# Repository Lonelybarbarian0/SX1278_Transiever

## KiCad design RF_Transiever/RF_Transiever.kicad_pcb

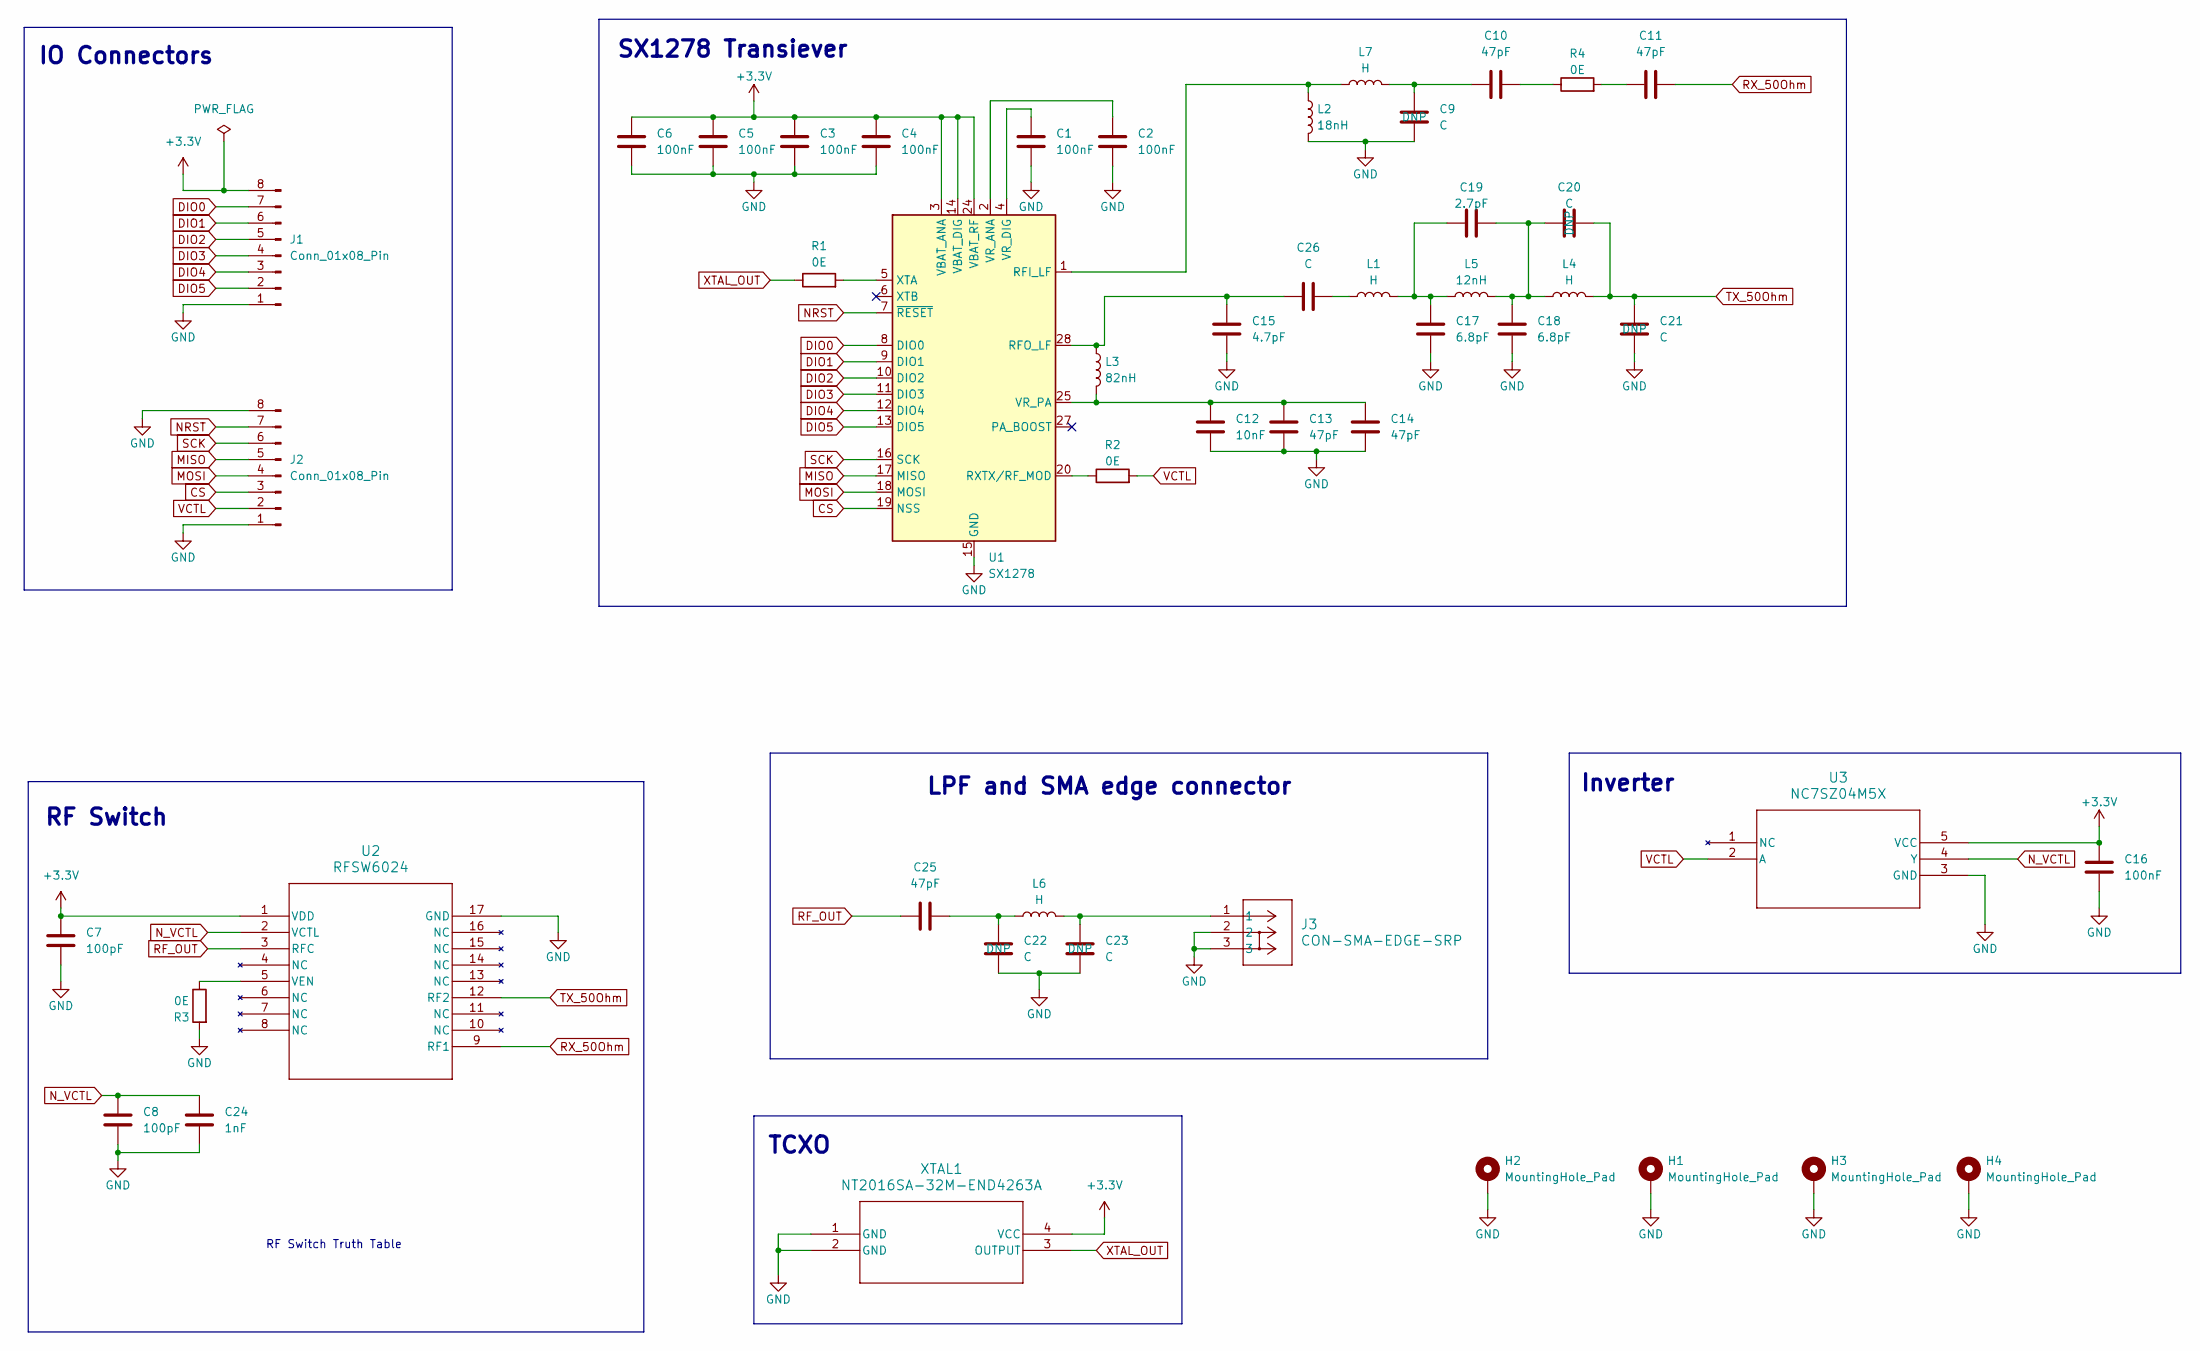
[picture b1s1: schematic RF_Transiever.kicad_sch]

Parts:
C1, C2, C3, C4, C5, C6, C16: 100nF; C_0402_1005Metric
C7, C8: 100pF; C_0402_1005Metric
C9, C20, C21, C22, C23, C26: C; C_0402_1005Metric
C10, C11, C13, C14, C25: 47pF; C_0402_1005Metric
C12: 10nF; C_0402_1005Metric
C15: 4.7pF; C_0402_1005Metric
C17, C18: 6.8pF; C_0402_1005Metric
C19: 2.7pF; C_0402_1005Metric
C24: 1nF; C_0402_1005Metric
H1, H2, H3, H4: MountingHole_Pad; MountingHole_2.2mm_M2_Pad
J1, J2: Conn_01x08_Pin; PinHeader_1x08_P2.54mm_Vertical
J3: CON-SMA-EDGE-SRP; CON-SMA-EDGE-SRP_RFS
L1, L4, L6, L7: H; L_0402_1005Metric
L2: 18nH; L_0402_1005Metric
L3: 82nH; L_0402_1005Metric
L5: 12nH; L_0402_1005Metric
R1, R2, R3: 0E; R_0603_1608Metric
R4: 0E; R_0402_1005Metric
U1: SX1278; QFN-28-1EP_6x6mm_P0.65mm_EP4.8x4.8mm
U2: RFSW6024; QFN16_4X4_QOR
U3: NC7SZ04M5X; SC-74A-5_1P65X3P15_ONS
XTAL1: NT2016SA-32M-END4263A; NT2016SA-32M-END4263A_NDK

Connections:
+3.3V: C3.1, C4.1, C5.1, C6.1, C7.1, C16.1, J1.8, U1.3 (VBAT_ANA), U1.14 (VBAT_DIG), U1.24 (VBAT_RF), U2.1 (VDD), U3.5 (VCC), XTAL1.4 (VCC)
CS: J2.3, U1.19 (NSS)
DIO0: J1.7, U1.8 (DIO0)
DIO1: J1.6, U1.9 (DIO1)
DIO2: J1.5, U1.10 (DIO2)
DIO3: J1.4, U1.11 (DIO3)
DIO4: J1.3, U1.12 (DIO4)
DIO5: J1.2, U1.13 (DIO5)
GND: C1.2, C2.2, C3.2, C4.2, C5.2, C6.2, C7.2, C8.2, C9.2, C12.2, C13.2, C14.2, C15.2, C16.2, C17.2, C18.2, C21.2, C22.2, C23.2, C24.2, H1.1, H2.1, H3.1, H4.1, J1.1, J2.1, J2.8, J3.2, J3.3, L2.2, R3.2, U1.15 (GND), U1.21 (GND), U1.22 (GND), U1.23 (GND), U1.26 (GND), U1.29 (GND), U2.17 (GND), U3.3 (GND), XTAL1.1 (GND), XTAL1.2 (GND)
MISO: J2.5, U1.17 (MISO)
MOSI: J2.4, U1.18 (MOSI)
NRST: J2.7, U1.7 (~RESET)
N_VCTL: C8.1, C24.1, U2.2 (VCTL), U3.4 (Y)
unnamed: C9.1, C10.1, L7.2
unnamed: C10.2, R4.1
unnamed: C11.1, R4.2
unnamed: C17.1, C19.1, L1.2, L5.1
unnamed: C18.1, C19.2, C20.1, L4.1, L5.2
unnamed: C22.1, C25.2, L6.1
unnamed: C23.1, J3.1, L6.2
unnamed: C26.2, L1.1
unnamed: L2.1, L7.1, U1.1 (RFI_LF)
unnamed: C15.1, C26.1, L3.1, U1.28 (RFO_LF)
unnamed: R2.1, U1.20 (RXTX/RF_MOD)
unnamed: C2.1, U1.2 (VR_ANA)
unnamed: C1.1, U1.4 (VR_DIG)
unnamed: C12.1, C13.1, C14.1, L3.2, U1.25 (VR_PA)
unnamed: R1.2, U1.5 (XTA)
unnamed: R3.1, U2.5 (VEN)
RF_OUT: C25.1, U2.3 (RFC)
RX_50Ohm: C11.2, U2.9 (RF1)
SCK: J2.6, U1.16 (SCK)
TX_50Ohm: C20.2, C21.1, L4.2, U2.12 (RF2)
VCTL: J2.2, R2.2, U3.2 (A)
XTAL_OUT: R1.1, XTAL1.3 (OUTPUT)

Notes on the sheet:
IO Connectors
Inverter
SX1278 Transiever
LPF and SMA edge connector
TCXO
RF Switch Truth Table
RF Switch

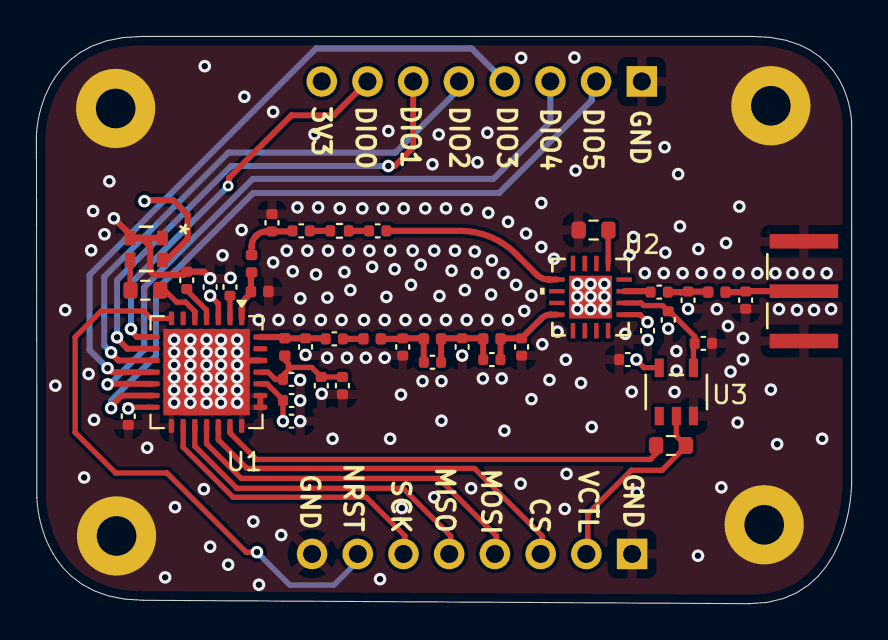
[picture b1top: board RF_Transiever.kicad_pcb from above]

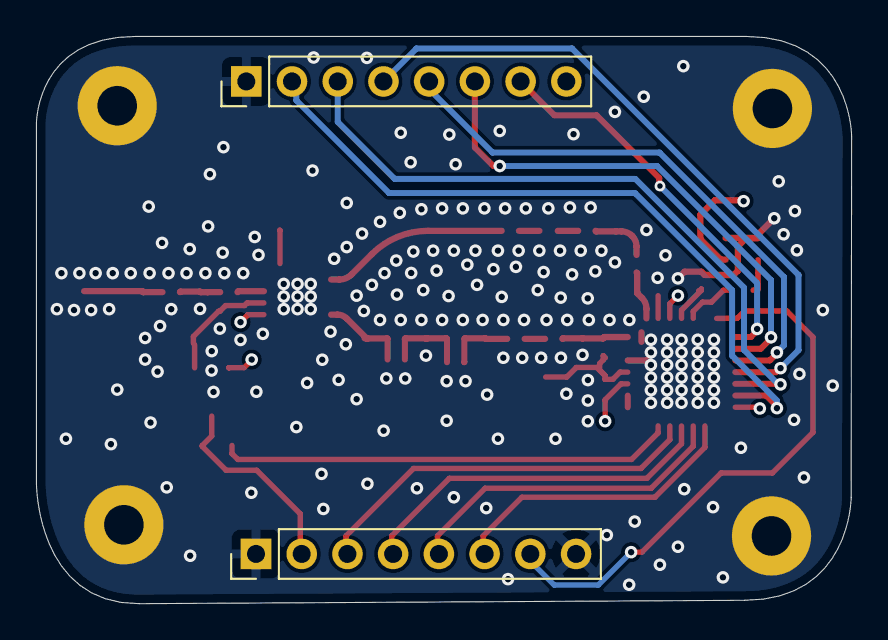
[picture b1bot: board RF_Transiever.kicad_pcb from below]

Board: 4 copper layers, 45.3 x 31.5 mm, 48 parts (2 on the bottom side), 35 nets.
